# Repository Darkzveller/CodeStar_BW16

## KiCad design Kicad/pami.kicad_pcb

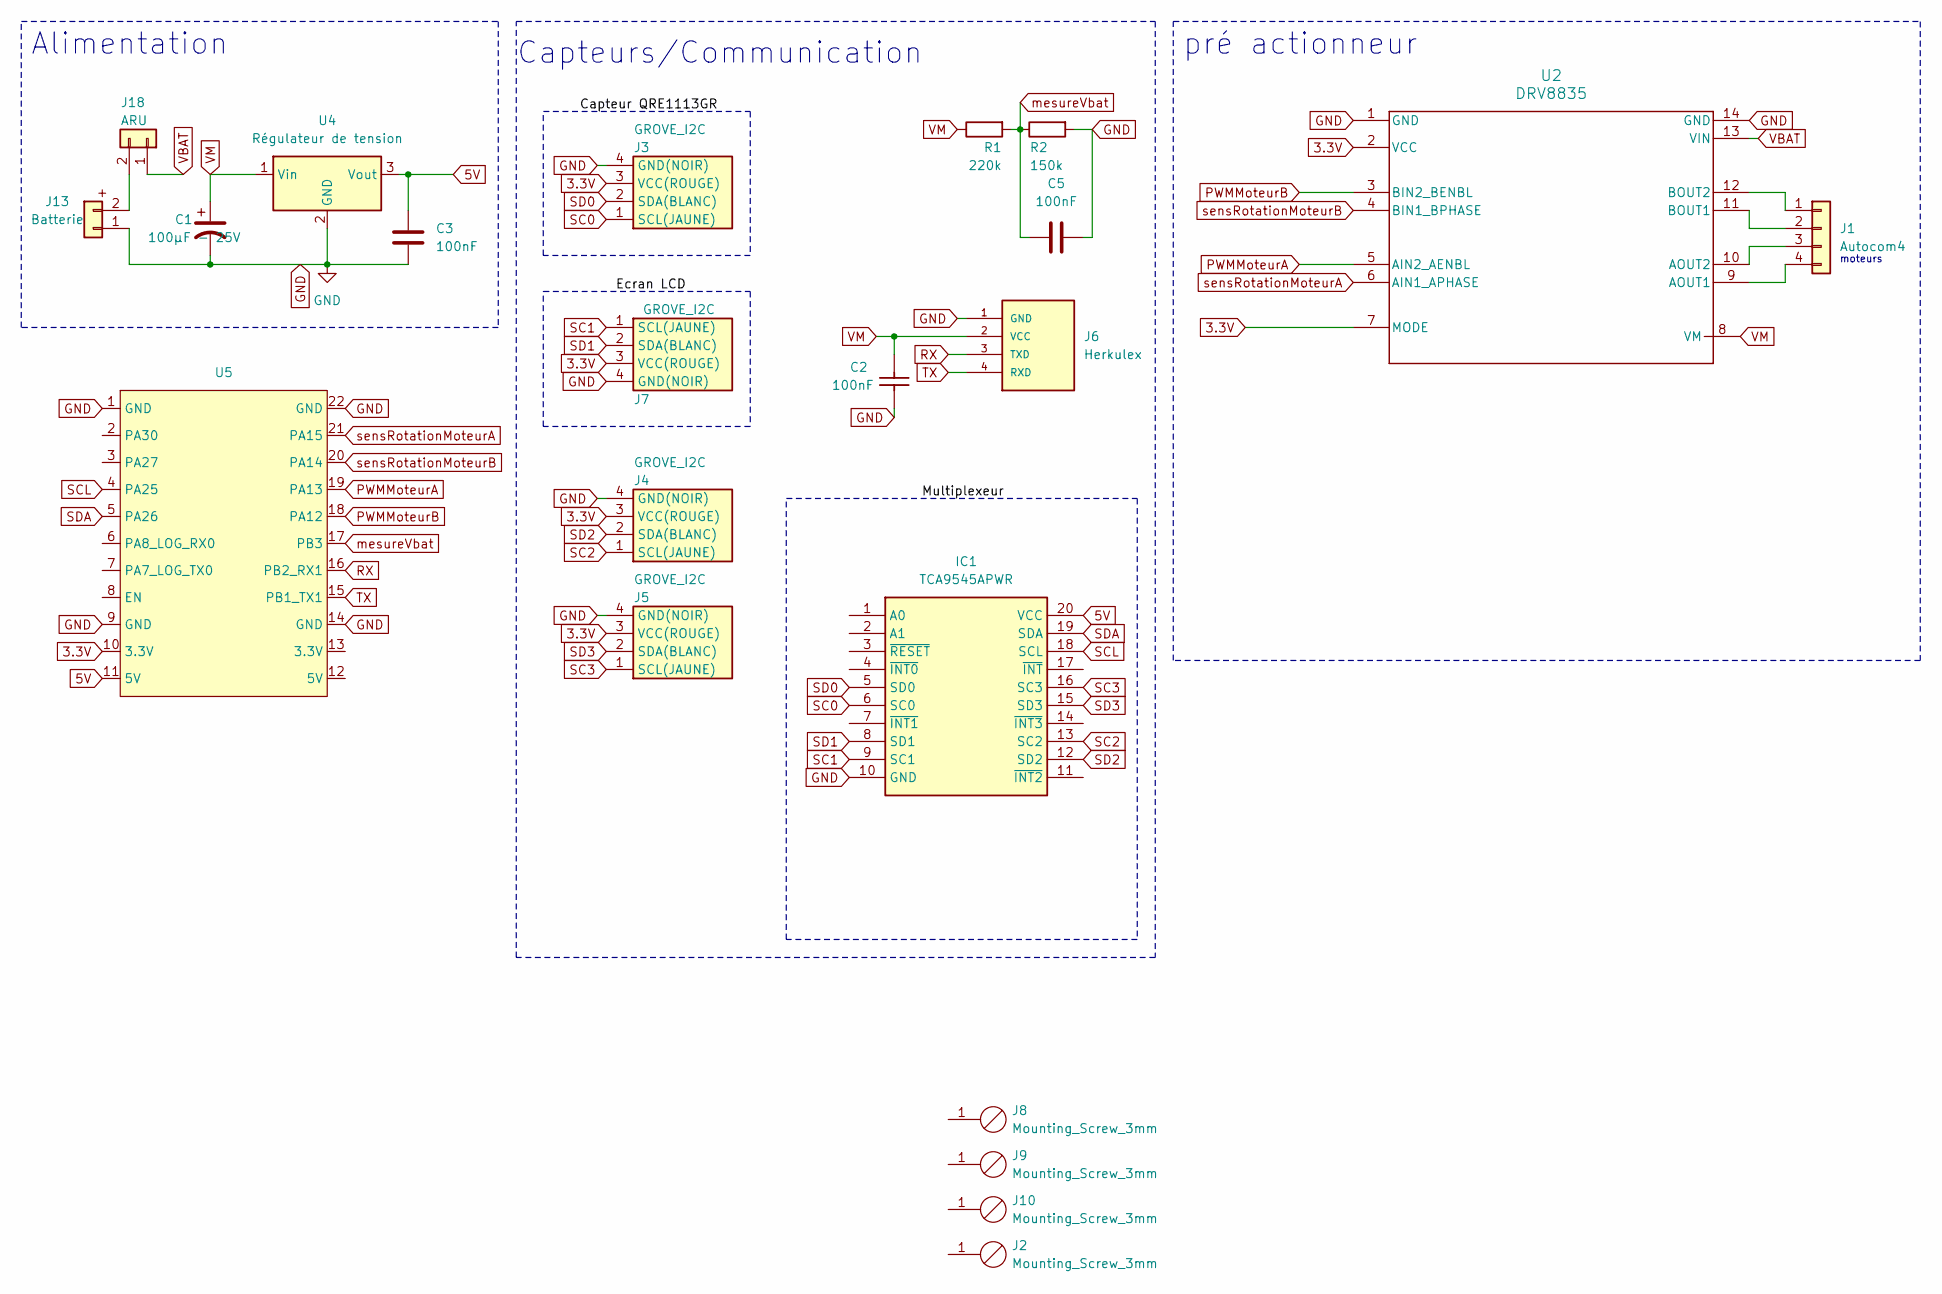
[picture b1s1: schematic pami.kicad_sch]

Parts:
C1: 100µF - 25V; CP_Radial_D10.0mm_P5.00mm
C2, C3, C5: 100nF; C_Rect_L7.0mm_W2.5mm_P5.00mm
IC1: TCA9545APWR; SOP65P640X120-20N; Mouser Part Number 595-TCA9545APWR
J1: Autocom4
J2, J8, J9, J10: Mounting_Screw_3mm
J3, J4, J5, J7: GROVE_I2C; SEEED_110990030
J6: Herkulex; TE_292161-4
J13: Batterie; OmnimateSL-5,08_1x02_P5.08mm_Vertical
J18: ARU; Autocom2
R1: 220k; R_Axial_DIN0207_L6.3mm_D2.5mm_P10.16mm_Horizontal
R2: 150k; R_Axial_DIN0207_L6.3mm_D2.5mm_P10.16mm_Horizontal
U2: DRV8835; DIP-14_W7.62mm
U4: Régulateur de tension; Converter_DCDC_TRACO_TSR-1_THT
U5: BW16

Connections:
3.3V: J3.3 (VCC(ROUGE)), J4.3 (VCC(ROUGE)), J5.3 (VCC(ROUGE)), J7.3 (VCC(ROUGE)), U2.2 (VCC), U2.7 (MODE), U5.10 (3.3V)
5V: C3.1, IC1.20 (VCC), U4.3 (Vout), U5.11 (5V)
GND: C1.2, C2.1, C3.2, C5.2, IC1.10 (GND), J3.4 (GND(NOIR)), J4.4 (GND(NOIR)), J5.4 (GND(NOIR)), J6.1 (GND), J7.4 (GND(NOIR)), J13.1, R2.2, U2.1 (GND), U2.14 (GND), U4.2 (GND), U5.1 (GND), U5.9 (GND), U5.14 (GND), U5.22 (GND)
unnamed: J1.1, U2.12 (BOUT2)
unnamed: J1.2, U2.11 (BOUT1)
unnamed: J1.3, U2.10 (AOUT2)
unnamed: J1.4, U2.9 (AOUT1)
unnamed: J13.2, J18.2
PWMMoteurA: U2.5 (AIN2_AENBL), U5.19 (PA13)
PWMMoteurB: U2.3 (BIN2_BENBL), U5.18 (PA12)
RX: J6.3 (TXD), U5.16 (PB2_RX1)
SC0: IC1.6 (SC0), J3.1 (SCL(JAUNE))
SC1: IC1.9 (SC1), J7.1 (SCL(JAUNE))
SC2: IC1.13 (SC2), J4.1 (SCL(JAUNE))
SC3: IC1.16 (SC3), J5.1 (SCL(JAUNE))
SCL: IC1.18 (SCL), U5.4 (PA25)
SD0: IC1.5 (SD0), J3.2 (SDA(BLANC))
SD1: IC1.8 (SD1), J7.2 (SDA(BLANC))
SD2: IC1.12 (SD2), J4.2 (SDA(BLANC))
SD3: IC1.15 (SD3), J5.2 (SDA(BLANC))
SDA: IC1.19 (SDA), U5.5 (PA26)
TX: J6.4 (RXD), U5.15 (PB1_TX1)
VBAT: J18.1, U2.13 (VIN)
VM: C1.1, C2.2, J6.2 (VCC), R1.1, U2.8 (VM), U4.1 (Vin)
mesureVbat: C5.1, R1.2, R2.1, U5.17 (PB3)
sensRotationMoteurA: U2.6 (AIN1_APHASE), U5.21 (PA15)
sensRotationMoteurB: U2.4 (BIN1_BPHASE), U5.20 (PA14)

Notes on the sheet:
Capteurs/Communication
pré actionneur
Alimentation
moteurs

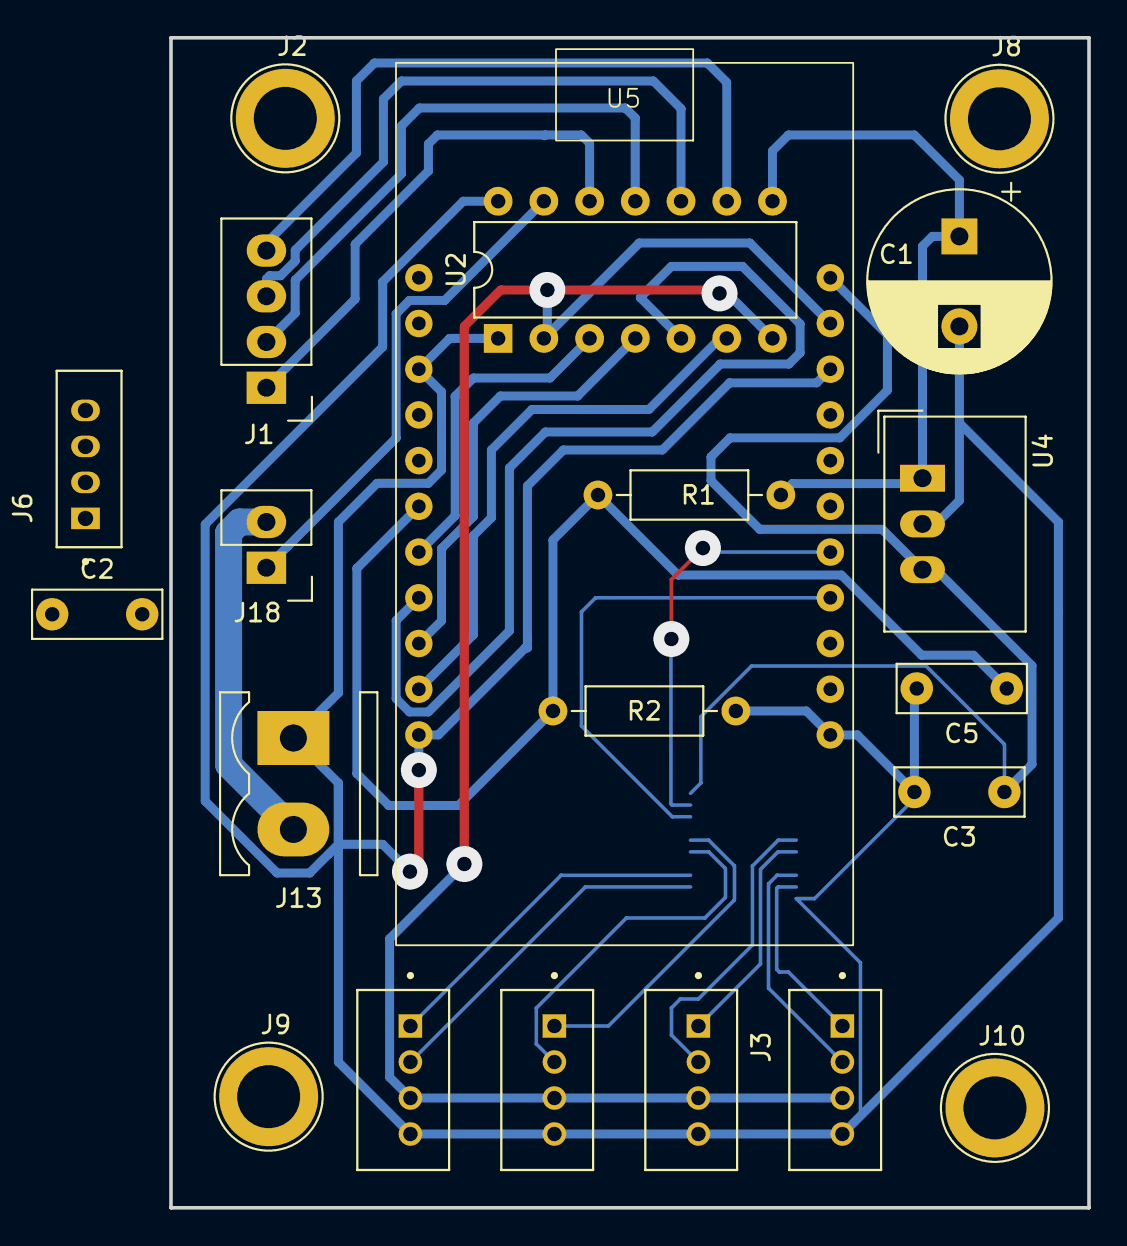
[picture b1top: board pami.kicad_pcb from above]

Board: 2 copper layers, 51.0 x 65.0 mm, 22 parts (1 on the bottom side), 27 nets.

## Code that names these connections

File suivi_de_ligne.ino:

#include <Wire.h>
#include <Adafruit_ADS1X15.h>
#include <Arduino.h>
#include "Vl53l0x.h"
#include "rgb_lcd.h"
#include "FreeRTOS.h"
#include "task.h"
#include <WiFi.h>

char* ssid = "cdf_crac";
const char* password = "cracadmin";
const char* wifiIP = "192.168.0.1";  // Adresse IP du serveur
const char* serverIP = "192.168.0.101";

const int wifiPort = 8080;    // Port utilisé pour tester la connexion WiFi
const int socketPort = 5050;  // Port utilisé pour le socket principal

WiFiClient wifiClient;    // Client pour tester la connexion WiFi (8080)
WiFiClient socketClient;  // Client pour le vrai socket (5050)



#define PWMG PA13
#define SWITCHG PA15
#define PWMD PA12
#define SWITCHD PA14
#define BRAS PA30

TaskHandle_t suivi_ligne = nullptr;

rgb_lcd lcd;

int nb_tof = 2;

int mesures[2];
Vl53l0x monCapteur[2];
VL53L0X_RangingMeasurementData_t measure;




// Crée un objet pour l'ADS1015
Adafruit_ADS1X15 ads;
float erreur = 0, erreurP = 0;
float commande = 0, kp = 3000, kd = 10000, ki = 0;
float mg = 0, md = 0;
int vmax = 200;
int suivi = 0;
float cgmax = 0, cgmin = 100000, cdmax = 0, cdmin = 100000;
float cg, cd;

// unsigned long intervalle = 1000;

//Vl53l0x monCapteur[2];

void read_tof() {
  for (int i = 0; i < nb_tof; i++) {
    monCapteur[i].performSingleRangingMeasurement(&measure);
    mesures[i] = measure.RangeMilliMeter;  // on range toutes les valeurs dans une liste
    // Serial.println(mesures[i]);            //on print les deux au cas où y ait une merde
  }
}

void init_tof() {

  //fonction pour lancer les tof ! Tout ce dont on a besoin c'est du nombre de tof à init

  for (int i = 0; i < nb_tof; i++) {  // jusqu'à ce qu'on soit à nb_tof -> mini est de 1 tof donc nb_tof = 1
    Wire.beginTransmission(0x70);
    Wire.write(1 << i);
    Wire.endTransmission();
    delay(1000);
    if (!monCapteur[i].begin(0x29, false)) Serial.print("good");  // on regarde si le démarrage est bon
    delay(1000);                                                  // delay obligatoire pour lui laisser le temps de bien boot
    monCapteur[i].changeAddress(0x50 + i);                        // on change l'adresse après le delay
  }

  Wire.beginTransmission(0x70);
  Wire.write(0x0F);  // le multiplexeur est entièrement ouvert
  Wire.endTransmission();

  delay(1000);  // delay pour laisser le temps au cas où
}

void etalonnage() {
  unsigned long maintenant = millis();
  unsigned long start = maintenant;

  while ((maintenant - start) < 10000) {
    maintenant = millis();
    float captDroit = ads.readADC_SingleEnded(0);   // Lire la valeur du canal A0
    float captGauche = ads.readADC_SingleEnded(1);  // Lire la valeur du canal A1

    if(captGauche > cgmax) cgmax = captGauche;
    if(captGauche < cgmin) cgmin = captGauche;
    if(captDroit > cdmax) cdmax = captDroit;
    if(captDroit < cdmin) cdmin = captDroit;

    Serial.println(maintenant-start);
  }
}

void suivi_de_ligne(void*) {
  unsigned long dernierTOF = 0;
  const unsigned long intervalleTOF = 100;  // 100 ms
  while (1) {
    ulTaskNotifyTake(pdTRUE, portMAX_DELAY);
    while (1) {
      int16_t captDroit = ads.readADC_SingleEnded(0);   // Lire la valeur du canal A0
      int16_t captGauche = ads.readADC_SingleEnded(1);  // Lire la valeur du canal A1

      cg = (float)((captGauche-cgmin)/(cgmax-cgmin));
      cd = (float)((captDroit-cdmin)/(cdmax-cdmin));

      unsigned long maintenant = millis();
      if (maintenant - dernierTOF >= intervalleTOF) {
        dernierTOF = maintenant;
        read_tof();  // lecture des distances TOF toutes les 100 ms
      }

      erreur = (float)cg - cd;
      commande = (float)(kp * erreur + kd * (erreur - erreurP));


      switch (suivi) {
        lcd.print("CaptG: ");
        lcd.println(captGauche);
        lcd.print("CaptD: ");
        lcd.println(captDroit);
        case 0:
          //delay(2000);
          suivi = 1;
          break;

        case 1:

          mg = (float)(vmax + commande);
          md = (float)(vmax - commande);

          if (mg > vmax) mg = vmax;
          if (md > vmax) md = vmax;
          if ((captGauche > 1100) & (captDroit > 1100)) suivi = 2;
          if ((mesures[0] < 100) & (mesures[1] < 100)) suivi = 4;
          erreurP = erreur;
          break;

        case 2:
          //delay(1000);
          mg = 108;
          md = 110;
          digitalWrite(SWITCHD, LOW);
          digitalWrite(SWITCHG, HIGH);
          analogWrite(PWMG, mg);
          analogWrite(PWMD, md);
          if ((mesures[0] < 100) & (mesures[1] < 100)) suivi = 4;
          delay(350);
          suivi = 3;
          break;
        case 3:
          mg = 0;
          md = 0;
          lcd.setRGB(0, 255, 0);
          lcd.print("C'est carreeee !");
          break;
        case 4:
          mg = 0;
          md = 0;
          if ((mesures[0] > 100) & (mesures[1] > 100)) suivi = 1;
          break;
      }
      digitalWrite(SWITCHD, LOW);
      digitalWrite(SWITCHG, HIGH);
      analogWrite(PWMG, mg);
      analogWrite(PWMD, md);
      vTaskDelay(pdMS_TO_TICKS(10));  // Pause de 10ms
    }
  }
}

void init_wifi() {

  // 🔹 Connexion au réseau WiFi
  WiFi.begin(ssid, password);
  Serial.print(" Connexion au WiFi");

  while (WiFi.status() != WL_CONNECTED) {
    delay(500);
    Serial.print(".");
  }

  Serial.println("\nConnecté au WiFi !");
  Serial.print("Adresse IP du BW16: ");
  Serial.println(WiFi.localIP());

  // 🔹 Tester la connexion sur le port 8080
  Serial.print("Connexion au serveur sur le port 8080... ");
  if (wifiClient.connect(wifiIP, wifiPort)) {
    Serial.println("Connexion réussie au port 8080 !");
    wifiClient.println("Test connexion WiFi OK");
  } else {
    Serial.println("Échec de connexion au port 8080.");
  }
}

void init_socket() {
  Serial.print("Connexion au serveur sur le port 5050... ");
  if (socketClient.connect(serverIP, socketPort)) {
    Serial.println("Connexion réussie au socket 5050 !");
    socketClient.println("Hello Server, je suis BW16 !");
  } else {
    Serial.println("Échec de connexion au socket 5050.");
  }
}

void read_socket(void*) {
  while (1) {
    if (socketClient.available()) {
      String response = socketClient.readString();
      if(response == "START_STAR" ) {
        xTaskNotifyGive(suivi_ligne);
      }
      if(response == "ETALO") {
        etalonnage();
      }
      //Serial.println("Réponse du serveur : " + response);
    }
    vTaskDelay(pdMS_TO_TICKS(100));  // Pause de 100ms
  }
}



void setup() {
  Serial.begin(115200);
  pinMode(SWITCHG, OUTPUT);
  pinMode(SWITCHD, OUTPUT);
  pinMode(PWMD, OUTPUT);
  pinMode(PWMG, OUTPUT);
  analogWrite(PWMD, 0);
  analogWrite(PWMG, 0);
  pinMode(BRAS, OUTPUT);  // attache le servo au pin spécifié
  analogWrite(BRAS, 0);
  // Wire.begin();  // Initialise le bus I2C
  Serial.begin(115200);

  Wire.begin();
  Wire.setClock(400000);
  Serial.println("Avant ADS");
  if (!ads.begin(ADS1X15_ADDRESS, &Wire, true)) {
    Serial.println("Erreur de communication avec l'ADS1015");
    while (1)
      ;
  }
  init_tof();
  init_wifi();
  init_socket();
  lcd.begin(16, 2, false);
  lcd.setRGB(255, 0, 0);
  lcd.setCursor(0, 0);
  lcd.print("Init OK !");
  delay(500);
  lcd.clear();
  xTaskCreate(suivi_de_ligne, "Suivi", 4096, NULL, 1, &suivi_ligne);
  xTaskCreate(read_socket, "Socket", 4096, NULL, 2, 0);
}



void loop() {
}
//   // lcd.setCursor(0, 0);
//   // lcd.print("Hello");










//   // analogWrite(BRAS, 250);
//   // delay(1000);
//   // analogWrite(BRAS, 50);
//   // delay(1000);
// }

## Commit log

2025-05-05 Ajout kicad de la star
2025-05-28 Modification GUINAND
2025-05-29 Homologation Star
2025-05-30 Affichage du score du match
2025-05-30 Code nouvelle carte capteurs avancés
2025-05-30 Star qui chante pour dernier match !
